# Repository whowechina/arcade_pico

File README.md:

# Arcade Pico - An Alternative Switch/Lamp Holder for Arcade Buttons
[点这里可以切换到中文版](README_CN.md)

It's the successor to my sanwa_opt project. With it, you can use regular low-profile keyboard switches (or even optical sensors) on arcade buttons.

## Features
* Compatible with both old Sanwa (push-click) and new Sanwa (twist-lock), Samducksa, and common Chinese buttons;
* Supports mechanical switches, optical sensors, and magnetic switches (`IO Board` required);
* Mechanical switch can be hotswap (Kailh Choc sockets);
* Feel switch and actuation switch can be separated;
* RGB LED support (`IO Board` required);
* FDM 3D-printing friendly.
* Multiple connection options to fit different systems.

## Thanks
Thanks to many respectful guys/companies who made their tools or materials free or open source (KiCad, OnShape, InkScape, Raspberry things).

Special thanks to community projects and developers.
And also these projects:
* RP_Silicon_KiCad: https://github.com/HeadBoffin/RP_Silicon_KiCad

## My Other Projects
You can check out my other cool projects.

* Popn Pico: https://github.com/whowechina/popn_pico
* IIDX Pico: https://github.com/whowechina/iidx_pico
* IIDX Teeny: https://github.com/whowechina/iidx_teeny
* Chu Pico: https://github.com/whowechina/chu_pico
* Mai Pico: https://github.com/whowechina/mai_pico
* Diva Pico: https://github.com/whowechina/diva_pico
* AIC Pico: https://github.com/whowechina/aic_pico
* Groove Pico: https://github.com/whowechina/groove_pico
* Geki Pico: https://github.com/whowechina/geki_pico
* Musec Pico: https://github.com/whowechina/musec_pico
* Ju Pico: https://github.com/whowechina/ju_pico
* Bishi Pico: https://github.com/whowechina/bishi_pico
* Nos Pico: https://github.com/whowechina/nos_pico
* Voltex Pico: https://github.com/whowechina/voltex_pico
* Chord Pico: https://github.com/whowechina/chord_pico
* Arcade Pico: https://github.com/whowechina/arcade_pico

## **Disclaimer** ##
I made this project in my personal time with no financial benefit or sponsorship. I will continue to improve the project. I have done my best to ensure that everything is accurate and functional, there's always a chance that mistakes may occur. I cannot be held responsible for any loss of your time or money that may result from using this open source project. Thank you for your understanding.

## About the License
It's CC-NC. So DIY for yourself and for your friend, don't make money from it. And plagiarism that doesn’t even dare to mention the original author is not acceptable. Please note that pooling orders and group buying for raw materials is acceptable.Selling any leftover components at cost (without profit) is also acceptable.

If you're interested in buying from me, or for commercial use, please contact me (Discord, QQ group, Goofish).
* My Discord Invitation: https://discord.gg/M8f2PPQFEA
* QQ Group: 854535476
* Goofish: whowe12345

## Use Cases
### Terminology First
* **`Main Board`** - The original controller board or IO board of your arcade system.
* **`Button Board`** - The PCB that contains the switch and LED daughter board. It's the major part of the Arcade Pico project.
* **`IO Board`** - The optional PCB that converts Hall effect switch signals to digital signals, and bridges regular LED signals to WS2812B RGB LED data signals. It's also part of the Arcade Pico project. It cannot replace your original `Main Board`.
* **`Lamp Holder`** - More accurately, it's a base equipped with both lamp and switch, but commonly referred to as lamp holder.

### Case: Replace the Lamp/Switch Holder without the `IO Board`
It's the most common and easy case. The only thing you need to do is wiring the switch and LED signals from your `Main Board` to the corresponding connectors on the `Button Board`.
You can use mechanical switches or optical sensors, but you can't use magnetic switches or RGB lights.

#### Wiring:
* **SW Out** (SH1.0 3P) on `Button Board` → **Button Input** on `Main Board`
* **LED In** (SH1.0 3P) on `Button Board` ← **Lamp Output** on `Main Board`

### Case: Enjoy the Magnetic Switch or the RGB light with the `IO Board`
With magnetic switch, you can define your trigger and reset distance. With RGB light, you can define your button light color and effect. `IO Board` is required to drive the magnetic switch and RGB light.

#### Wiring:
* Magnetic switch signals
  * **SW Out** (SH1.0 3P) on `Button Board` → **Hall In** (SH1.0 3P) on `IO Board`
  * **Out** (XH2.5 2P) on `IO Board` → **Button Input** on `Main Board`
* RGB LED signals
  * **Lamp Output** on `Main Board` → **Lamp In** (XH2.5 2P) on `IO Board`
  * **LED Out** (SH1.0 3P) on `IO Board` → **LED In** (SH1.0 3P) on `Button Board`
  * **LED Out** (SH1.0 3P) on `Button Board` → **LED In** (SH1.0 3P) on next `Button Board` (if any)
  * **LED Out** (SH1.0 3P) on last `Button Board` → **LED End** (SH1.0 3P) on `IO Board` for power backup.

* You can power the `IO Board` from the `Main Board`'s 5V supply via JST 2P, or directly via Type-C port (USB or power adapter).

#### When `IO Board` is connected to a host computer via Type-C:
  * `IO Board` works as an HID device.  
    So if you're fine with this extra USB cable, you might be able to skip the wiring between the `IO Board` and the `Main Board`. However, some games require the controller to be a single device, so this won't work in those cases.
  * CLI (command line interface) is on USB CDC (serial).
  * The Type-C port is also for firmware update.

### Imagined Case: Interfacing with DJDao PhoenixWAN
This is a theoretical case that probably won't be implemented. If implemented, all that cockamamie wiring between `IO Board` and `Main Board` would be eliminated - they'd simply communicate via UART.

Let's hope this happens someday.

# How to Build
## The Button Board
### Common Part
* The PCB gerber file is `Production/PCB/"arcade_pico_button_*.zip`. The one with `socket` is hotswap (for Choc V1 and V2). I always use JLC (https://www.jlcpcb.com) and Jiepei (https://www.jiepei.com), feel free to use your preferred PCB manufacturer. They may ask if you need half-hole pads for the `Button Board`, just answer "No", it's costy and not necessary.
* 2X 3P SH1.0 horizontal SMD connector on "SW" and "LED In" footprints.
* 1X 3P SH1.0 horizontal SMD connector on "LED Out" footprint, only needed when using WS2812B RGB LED daughter board.

* To connect LEDs:
  * "LED In" connector (+, -) is for regular single color LED signal from your existing `Main Board`.
  * "LED In" and "LED Out" connectors are for daisy-chain when using WS2812B RGB LED daughter board.

### Mechanical Switch
* Use either SW1 or SW2 footprint for Kailh Choc V1/V2 switches.
* Use Kailh Choc low-profile hotswap socket if you choose hotswap PCB version.  
  https://kailhswitch.net/products/kailh-mechnical-keyboard-switches-hot-swap-pcb-socket-diy-for-1350-choc-low-profile-keyboard-switches
* Short the corresponding jumper (sw1 or sw2) to enable the switch.
* You can solder the other switch, but it's only for the feel, so don't short the jumper.

* To connect to controller's `Main Board`:
  * "SW" connector (Out, GND) is for the switch signal;

* This example shows SW1 as the trigger switch, and optional Choc V1 on SW2 is just for the feel.  

### Optical Sensor (IR Diode + Phototransistor)
* Solder the IR diode (IR908-7C) and phototransistor (PT908-7C) at proper height;
* Solder R3 (500 ohm for 3.3V supply, 1k ohm for 5V supply);
* Resistors: R4, R5; Jumpers: c, e; Zener: Z1.
  * Low-active logic (most systems are): R4 (0-10 ohm), R5 (2k ohm), short the jumper e by soldering.
  * High-active logic: R4 (2k ohm), R5 (0-10 ohm), short the jumper c.
  * When power supply is 5V but the target system IO is 3.3V, solder Z1 (3.3V SOD-123F Zener diode) to protect the IO pin.
* You can solder a mechanical switch on SW1 footprint for some tactile feel, but don't short the jumper sw1.
* On most systems, LED positive line is a constant 5V or 3.3V power supply, you can borrow that to power the optical sensor - just short the jumper "LEDP-V".

* To connect to controller's `Main Board`:
  * "SW" connector (V, Out, GND) is for the switch signal;

* This example shows a low-active configuration, 5V is borrowed from LED positive line, and optional Choc V1 on SW1 just for the feel.  

### Magnetic (Hall Effect) Switch
* Magnetic switch is on SW1 footprint.
* Solder U1 (SS49E SOT23-3) and C1 (0.1uF 0603).
* You can install a mechanical switch on SW2 footprint for some tactile feel, but don't solder the jumper.
* If the Hall effect switch is not mounted tightly, you may need to use some RTV silicone adhesive to secure it.

* This example uses Hall effect switch on SW2 and optional Choc V1 on SW1 just for the feel.  

* To connect to controller's `Main Board`:
* "SW" connector (V, Out, G) connects to the **Arcade Pico IO** board. Then the `IO Board` connects to the `Main Board`.

* Note that Arcade Pico `IO Board` is need for this setup.

## The LED Daughter Board
* It is separated from the **Arcade Pico Button** board by snapping or cutting. There're two versions: single-color LED and WS2812B RGB LED. You can choose either one according to your needs.
* After soldering the components, insert the LED daughter board back to the button PCB vertically from the top side. Solder one pin first, so you'll have a chance to adjust the height.
* If it's too low or too high, you won't get even illumination. You can measure the height from your old lamp holder. From my experience with Sanwa, distance from the LED top to the PCB surface is about 37mm.
* When you finish adjusting the height, solder all pins to secure the connection.  

### Single-color LED Board
* Use high-brightness side emitting LEDs. The footprint is compatible with various packages, such as SMD 4008, SMD 4020, SMD 3014, or even through-hole ones (ones with concave lens are better).
* If you're using SMD LEDs, you can use two of them, one for each side, to get better light distribution.
* They're normally rated for 20mA current. So typically you use 100-220 ohm current resistors (R1 and R2) for 5V supply, or 50-100 ohm for 3.3V supply.
* Here's how it looks after soldered.  
    
* If the polarity of the LED footprint doesn't match your LED, just cut/break the copper trace right at the "x" mark at **both sides**, and short the jumpers accordingly. This will reverse the polarity.  

### WS2812B RGB LED Board
* **Arcade Pico `IO Board` is required.**
* Use WS2812B 4020 side emitting RGB LEDs. You can use two of them, one for each side, to get better light distribution.
* 0.1uF 0805 or 0603 capacitor on C2 footprint is highly recommended.
* Here's how it looks after soldered.  

## The `IO Board`
* The `IO Board` can convert the analog signals from Hall effect switches into digital signals for your main controller board. It can also bridge traditional LED bulb signals to WS2812B RGB LED data signals.
* If you don't need one or both of these functions, just skip the corresponding components.

### Common Parts
* 1x Raspberry Pi Pico.  
  https://www.raspberrypi.com/products/raspberry-pi-pico
* 2x 2P JST XH2.54 or XH2.5 vertical connectors, for 5V power input.
* 1x 3P JST XH2.54 or XH2.5 vertical connector for UART, optional for future use.

### Components for Hall Effect Switch
* 1x ADG708BRUZ, 8 to 1 analog switch, in TSSOP-16 (U3).
* 1x LP5907MFX-4.5 or TPS7A2042PDBVR LDO, in SOT23-5 (U2), see next line.
* 1x LM4040 shunt voltage reference in SOT23-3 (Z2), 2.0~2.1V (for 4.2V LDO) or 2.2~2.5V (for 4.5V LDO).
* 1x 3.3V Zener diode, in SOD-123 or SOD-123F, such as BZT52H-C3V3 (Z1).
* 3x 0.1uF 0603 capacitors (CC1, CC2, CC3).
* 8x 3P SH1.0 horizontal SMD connectors (In1~In8), for connecting up to 8 Hall effect `Button Board`s.
* 8x 2P JST XH2.54 or XH2.5 vertical connectors (Out1~Out8), for connecting to the main controller board.

### Components for RGB LED
* 8x 220ohm 0603 resistors (R1~R8), for optical isolator current limiting. If your light is 12V, use 1kohm 0805 resistors instead.
* 8x 1N4148 SOD-323 diodes (D1~D8), to protect from reverse voltage, only needed for 12V light input.
* 2X PC847 or compatible quad optical isolators (U4, U5), in SOP-16.
* 2x 0805 x 4 5.1K 8P4R resistor arrays (RN1, RN2), if they're not available, use 8x individual 5.1K 0603 resistors instead.
* 2x 3P SH1.0 horizontal SMD connectors (LED Out and LED End), to connect to the `Button Board` equipped with WS2812B RGB LED daughter board.
* 8x 2P JST XH2.54 or XH2.5 vertical connectors (Lamp In 1~8), for connecting to the main controller board's LED signal.

## Notes on PCB and Electronics
### Things You May **Need** to Tinker with
* Here's how you calculate the LED current limiter, it also applies to the IR emitter diode of the optical isolator:
  * R = (V_supply - V_F) / I
  * V_F for single color LED is usually around 3V, V_F for IR emitter is usually around 1.3V.
  * I for single color LED is usually 10-20mA, I for IR emitter is practically 1-10mA.
* Here's how you calculate the pull-up or pull-down resistor for phototransistor (the one on the `Button Board` and the one inside the optical isolator):
  * R >= V_supply / I_C
  * It's difficult to estimate the I_C (collector current) of the phototransistor, so just assume it's around 1mA.
  * So on a 3.3V power supply, R >= 3.3V / 1mA = 3.3K ohm, You can use a 3.3K or 3.9K ohm resistor.
  * You may need to adjust the resistor value according to your actual setup.

### Things You May **Want** to Tinker with
* For the "feel switch", choose clicky ones, Choc V1 and Choc V2 both have some clikcy options. If you find other low-profile mechanical switches which fit in the footprint, you can try them too.
* When Hall effect switch and the "feel" switch is both installed, spring force adds up, you may want to use a lighter spring for both of them. You can choose light force switches, or you can change the spring inside them.

## The Holder Body
* Use any FDM printer to print the body.
  * Material: PLA, PETG, ABS, you name it.
  * Layer Height: 0.2mm is recommended.
  * Infill: 20% is enough.
  * Walls: 2-4 perimeters.
  * Support: Yes, tree support.

* Files are in the "Production/3DPrint" folder.
  * `Sanwa_push.stl` - old style Sanwa lamp holder (push-click type).
  * `Sanwa_twist.stl` - new style Sanwa lamp holder (twist-lock type).
  * `Samducksa.stl` - Samducksa lamp holder.
  * `Chinese.stl` - common Chinese button lamp holder.

* Use M2\*6mm screws to secure the PCB to the button.

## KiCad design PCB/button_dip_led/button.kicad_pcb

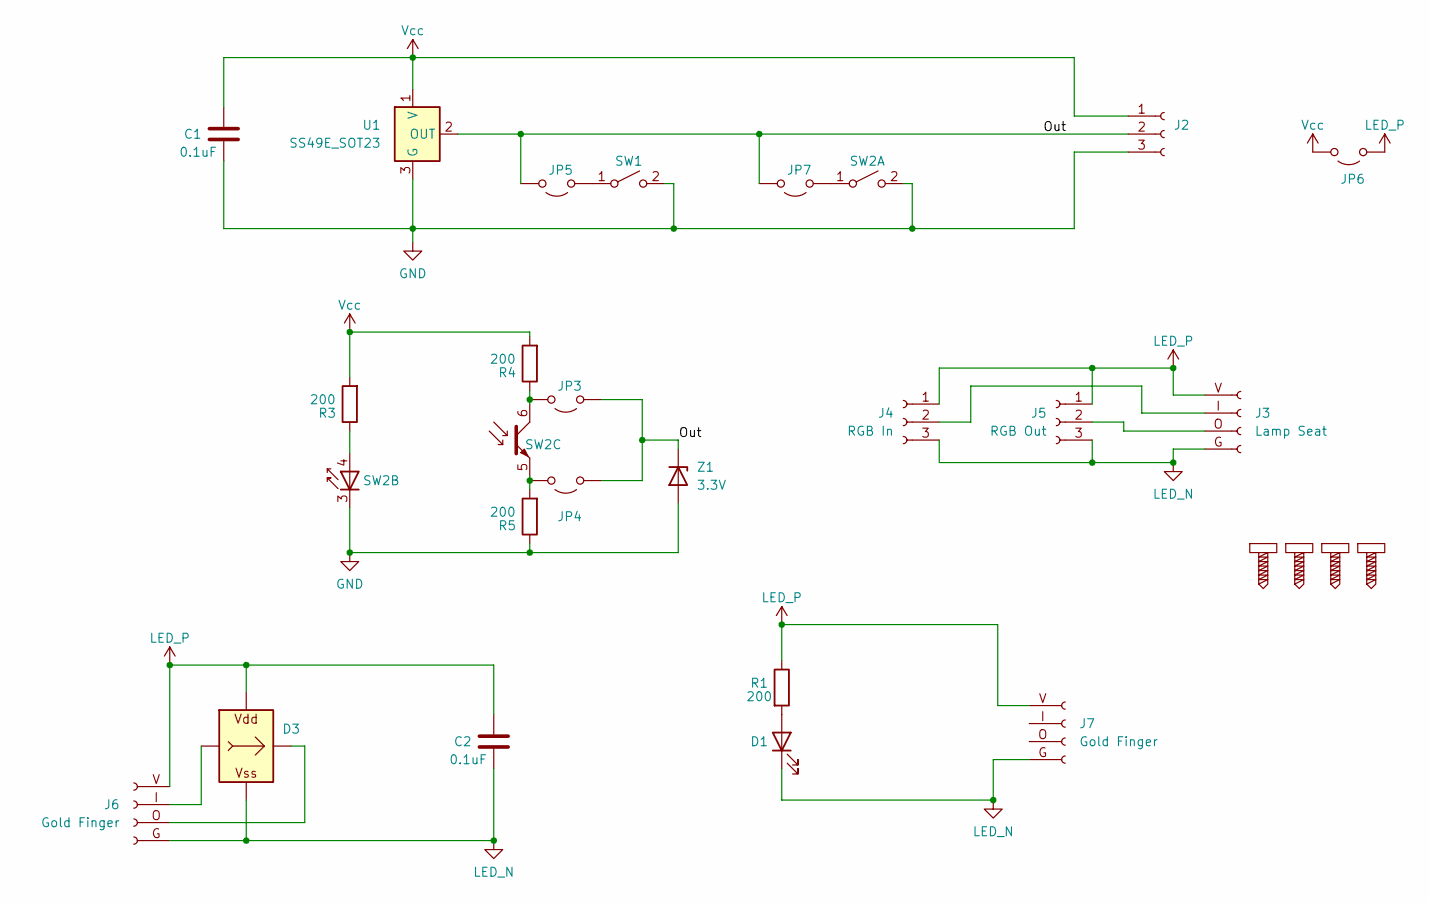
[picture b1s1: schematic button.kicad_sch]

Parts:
C1: 0.1uF; C_0603_1608Metric_Pad1.08x0.95mm_HandSolder
C2: 0.1uF; C_0805_2012Metric_Pad1.18x1.45mm_HandSolder
D1: LED; DIPLED
D3: WS2812B_Unified; WS2812B-DIP
J2: Conn_01x03_Socket; SH1.0_3P_Solder_Combo
J3: Lamp Seat; LampSeat
J4: RGB In; SH1.0_3P_Solder_Combo
J5: RGB Out; SH1.0_3P_Solder_Combo
J6, J7: Gold Finger; GoldFinger
JP3: c; SolderJump
JP4: e; SolderJump
JP5: sw1; SolderJump
JP6: LEDP-V; SolderJump
JP7: sw2; SolderJump
R1, R3: 200; R_0805_2012Metric_Pad1.20x1.40mm_HandSolder
R4, R5: 200; R_0805_2012Metric
S1, S2, S3, S4: M2_Screw
SW1: Choc_HE
SW2: Choc and IR Pair; SW_Kailh_Choc_IR_Combo
U1: SS49E_SOT23; SOT-23-FAT
Z1: 3.3V; D_SOD-123F

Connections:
/Out: J2.2, JP3.1 (A), JP4.1 (A), JP5.2 (B), JP7.2 (B), U1.2 (OUT), Z1.1 (K)
GND: C1.1, J2.3, R5.1, SW1.2 (B), SW2.2 (B), SW2.3 (K), U1.3 (G), Z1.2 (A)
LED_N: C2.1, D1.1 (K), D3.G (VSS), J3.G, J4.3, J5.3, J6.G, J7.G
LED_P: C2.2, D3.V (VDD), J3.V, J4.1, J5.1, J6.V, J7.V, JP6.1 (A), R1.1
unnamed: D1.2 (A), R1.2
unnamed: D3.I (In), J6.I (In)
unnamed: D3.O (Out), J6.O (Out)
unnamed: J3.I (In), J4.2
unnamed: J3.O (Out), J5.2
unnamed: JP3.2 (B), R4.1, SW2.6 (C)
unnamed: JP4.2 (B), R5.2, SW2.5 (E)
unnamed: JP5.1 (A), SW1.1 (A)
unnamed: JP7.1 (A), SW2.1 (A)
unnamed: R3.1, SW2.4 (A)
Vcc: C1.2, J2.1, JP6.2 (B), R3.2, R4.2, U1.1 (V)

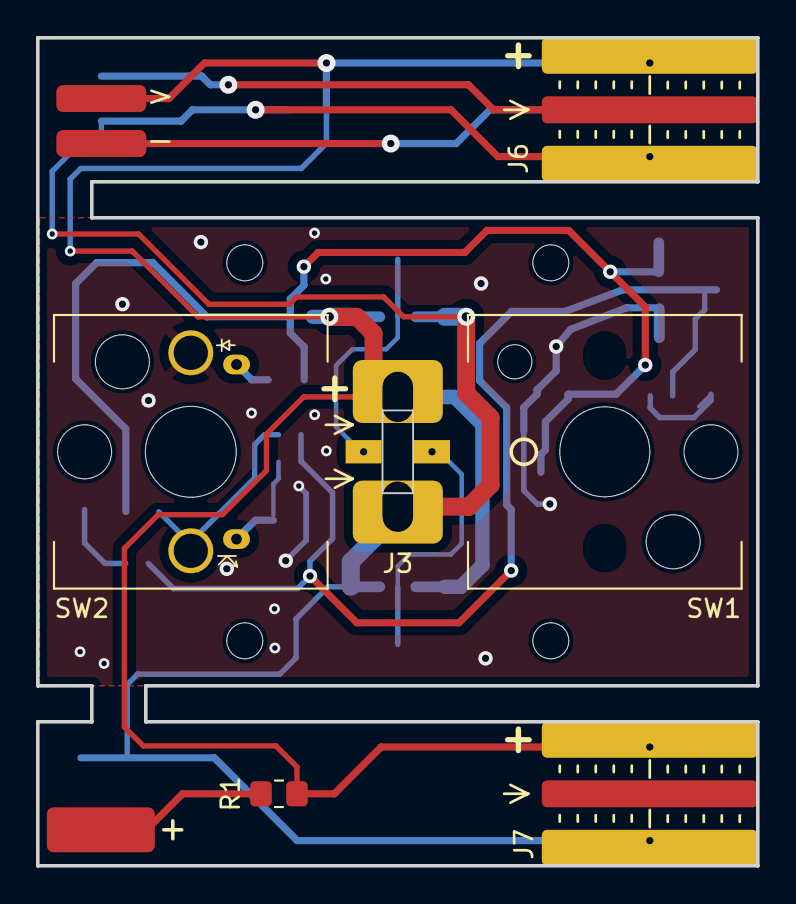
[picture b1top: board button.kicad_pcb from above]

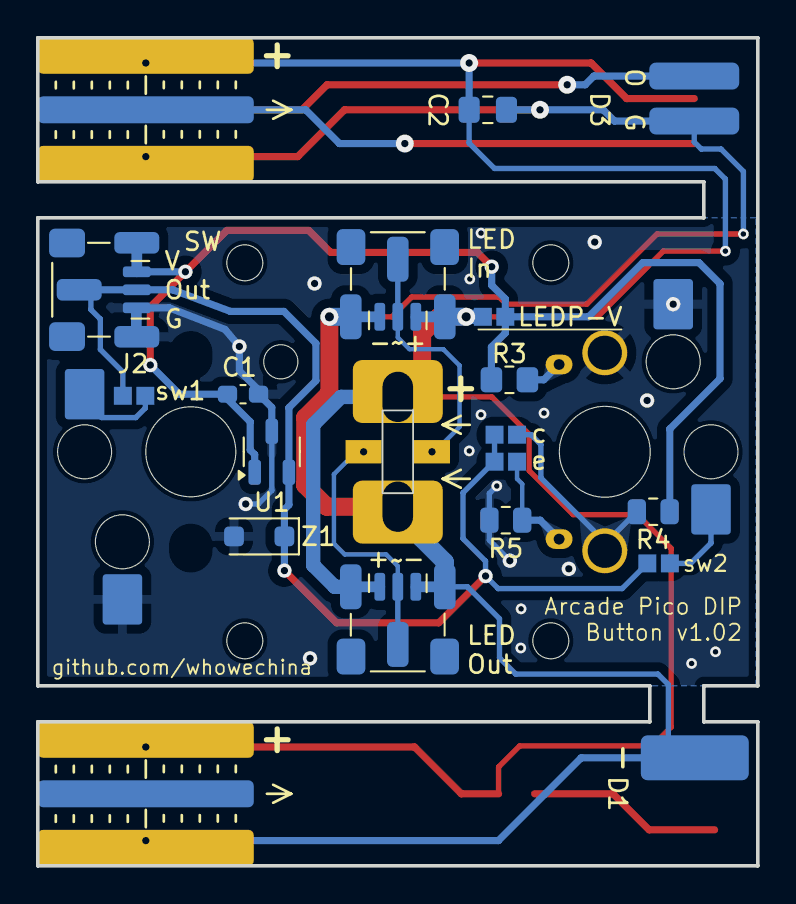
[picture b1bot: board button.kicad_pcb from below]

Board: 2 copper layers, 40.0 x 46.0 mm, 27 parts (17 on the bottom side), 15 nets.

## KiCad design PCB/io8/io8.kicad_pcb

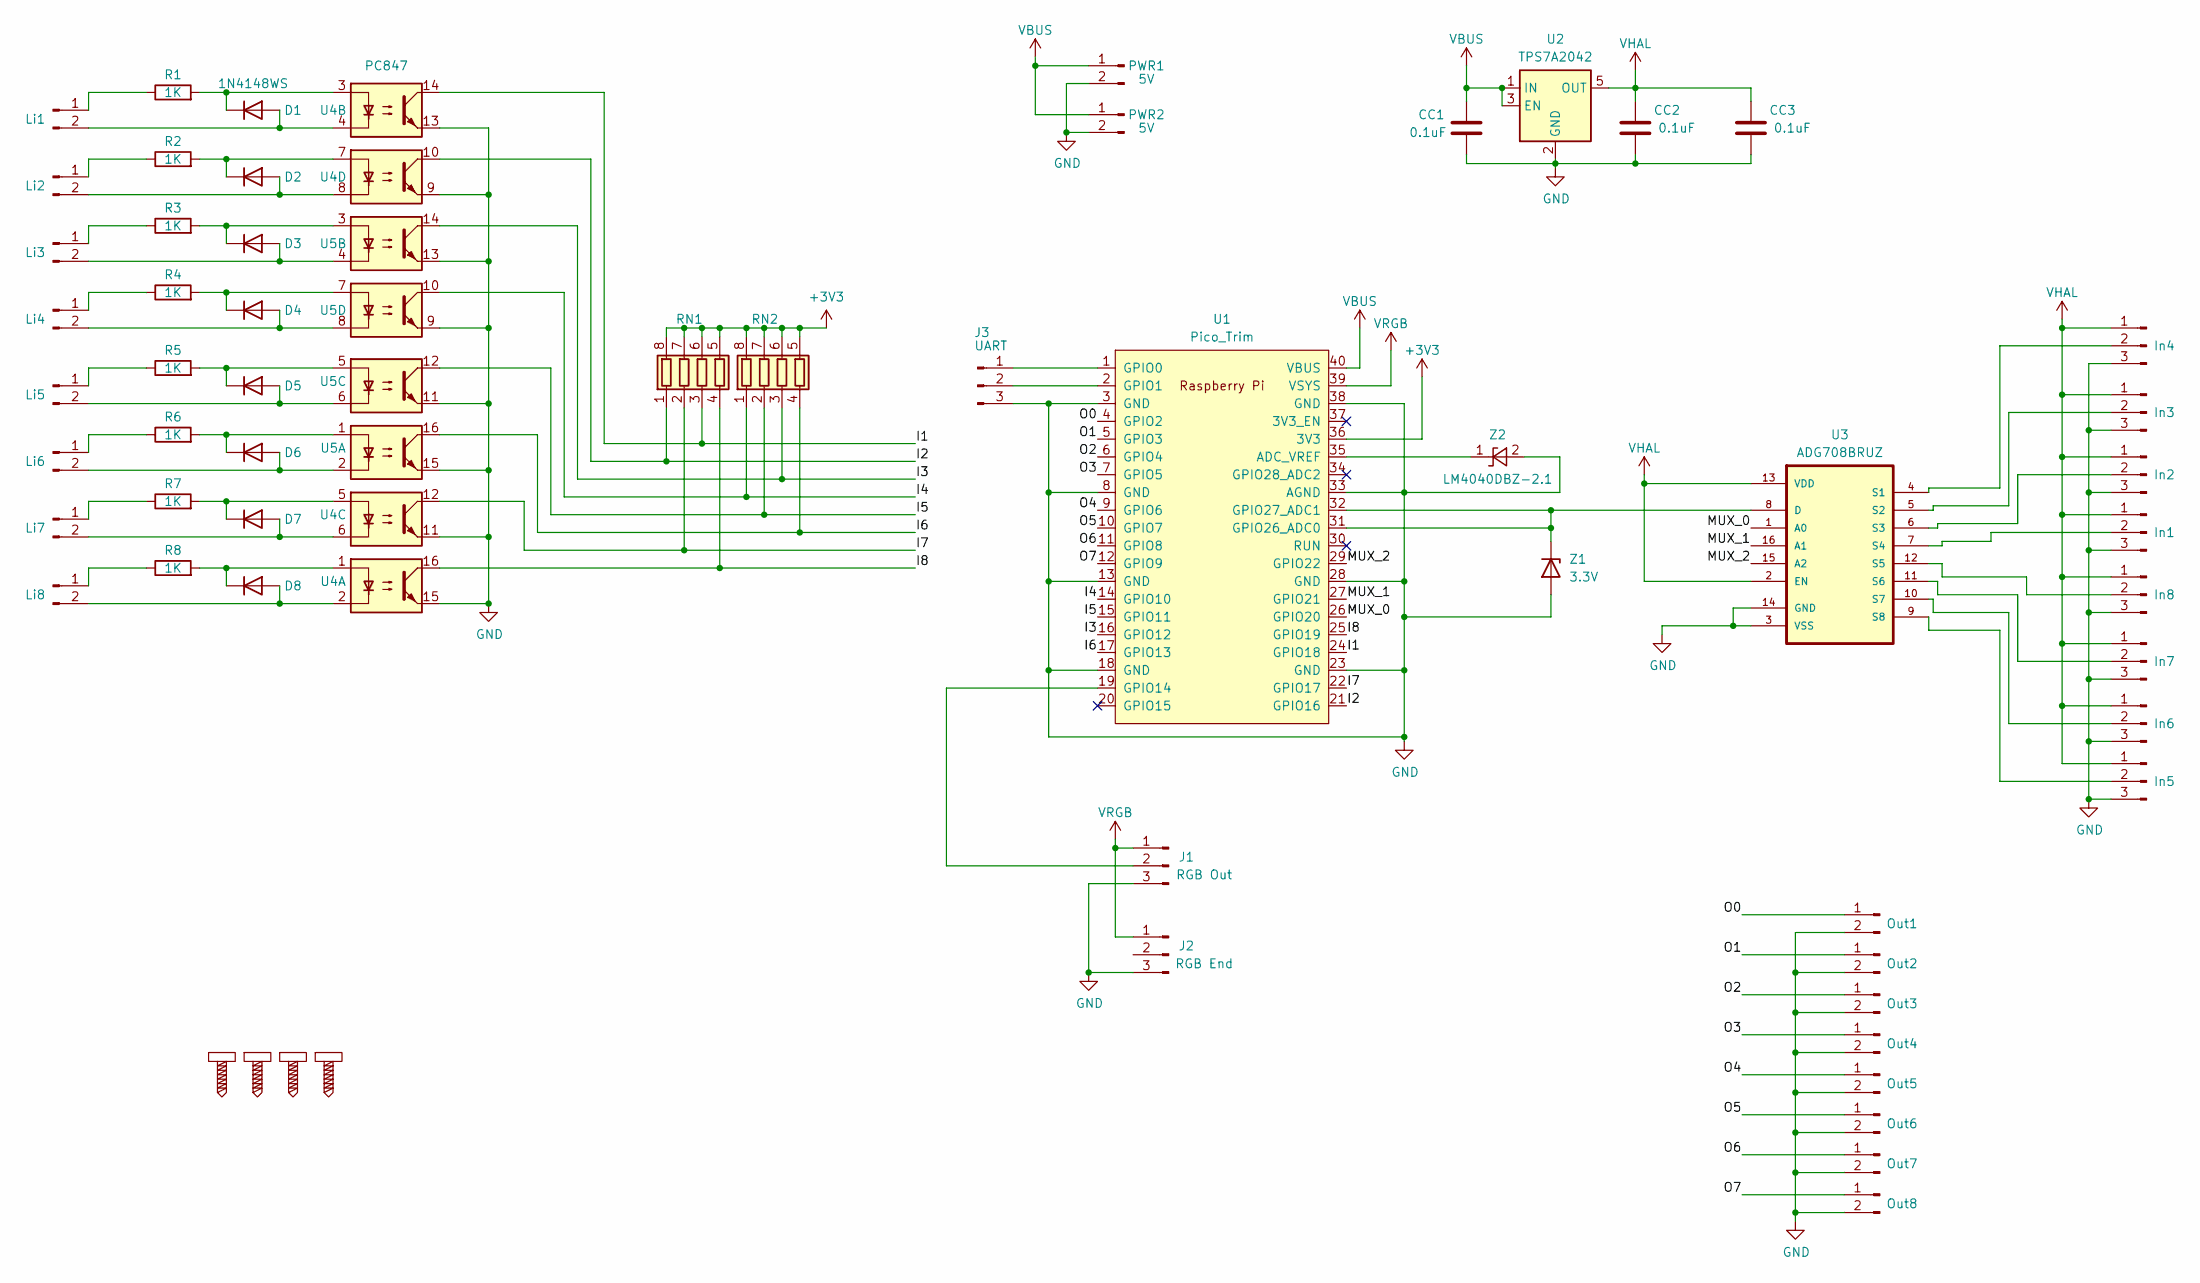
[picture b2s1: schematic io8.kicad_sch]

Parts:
CC1, CC2, CC3: 0.1uF; C_0603_1608Metric_Pad1.08x0.95mm_HandSolder
D1, D2, D3, D4, D5, D6, D7, D8: 1N4148WS; D_SOD-323_FAT
In1, In2, In3, In4, In5, In6, In7, In8: Conn_01x03_Pin; SH1.0_3P_Solder_Combo
J1: RGB Out; SH1.0_3P_Solder_Combo
J2: RGB End; SH1.0_3P_Solder_Combo
J3: UART; JST_XH_B3B-XH-A_1x03_P2.50mm_Vertical
Li1, Li2, Li3, Li4, Li5, Li6, Li7, Li8: Conn_01x02_Pin; JST_XH_B2B-XH-A_1x02_P2.50mm_Vertical
Out1, Out2, Out3, Out4, Out5, Out6, Out7, Out8: Conn_01x02_Pin; JST_XH_B2B-XH-A_1x02_P2.50mm_Vertical
PWR1, PWR2: 5V; JST_XH_B2B-XH-A_1x02_P2.50mm_Vertical
R1, R2, R3, R4, R5, R6, R7, R8: 1K; R_0805_2012Metric_Pad1.20x1.40mm_HandSolder
RN1, RN2: R_Pack04; R_Array_Convex_4x0805
S1, S2, S3, S4: M3_Screw
U1: Pico_Trim; RPi_Pico_SMD_No_USB
U2: TPS7A2042; SOT-23-5
U3: ADG708BRUZ; TSSOP-16_4.4x5mm_P0.65mm
U4, U5: PC847; SOP-16_4.4x10.4mm_P1.27mm
Z1: 3.3V; D_SOD-123F
Z2: LM4040DBZ-2.1; SOT-23-FAT

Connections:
+3V3: RN1.5 (R4.2), RN1.6 (R3.2), RN1.7 (R2.2), RN1.8 (R1.2), RN2.5 (R4.2), RN2.6 (R3.2), RN2.7 (R2.2), RN2.8 (R1.2), U1.36 (3V3)
/I1: RN1.3 (R3.1), U1.24 (GPIO18), U4.14
/I2: RN1.1 (R1.1), U1.21 (GPIO16), U4.10
/I3: RN2.3 (R3.1), U1.16 (GPIO12), U5.14
/I4: RN2.1 (R1.1), U1.14 (GPIO10), U5.10
/I5: RN2.2 (R2.1), U1.15 (GPIO11), U5.12
/I6: RN2.4 (R4.1), U1.17 (GPIO13), U5.16
/I7: RN1.2 (R2.1), U1.22 (GPIO17), U4.12
/I8: RN1.4 (R4.1), U1.25 (GPIO19), U4.16
/MUX_0: U1.26 (GPIO20), U3.1 (A0)
/MUX_1: U1.27 (GPIO21), U3.16 (A1)
/MUX_2: U1.29 (GPIO22), U3.15 (A2)
/O0: Out1.1, U1.4 (GPIO2)
/O1: Out2.1, U1.5 (GPIO3)
/O2: Out3.1, U1.6 (GPIO4)
/O3: Out4.1, U1.7 (GPIO5)
/O4: Out5.1, U1.9 (GPIO6)
/O5: Out6.1, U1.10 (GPIO7)
/O6: Out7.1, U1.11 (GPIO8)
/O7: Out8.1, U1.12 (GPIO9)
GND: CC1.2, CC2.2, CC3.2, In1.3, In2.3, In3.3, In4.3, In5.3, In6.3, In7.3, In8.3, J1.3, J2.3, J3.3, Out1.2, Out2.2, Out3.2, Out4.2, Out5.2, Out6.2, Out7.2, Out8.2, PWR1.2, PWR2.2, U1.3 (GND), U1.8 (GND), U1.13 (GND), U1.18 (GND), U1.23 (GND), U1.28 (GND), U1.33 (AGND), U1.38 (GND), U2.2 (GND), U3.3 (VSS), U3.14 (GND), U4.9, U4.11, U4.13, U4.15, U5.9, U5.11, U5.13, U5.15, Z1.2 (A), Z2.2 (A)
unnamed: D1.2 (A), Li1.2, U4.4
unnamed: D1.1 (K), R1.2, U4.3
unnamed: D2.2 (A), Li2.2, U4.8
unnamed: D2.1 (K), R2.2, U4.7
unnamed: D3.2 (A), Li3.2, U5.4
unnamed: D3.1 (K), R3.2, U5.3
unnamed: D4.2 (A), Li4.2, U5.8
unnamed: D4.1 (K), R4.2, U5.7
unnamed: D5.2 (A), Li5.2, U5.6
unnamed: D5.1 (K), R5.2, U5.5
unnamed: D6.2 (A), Li6.2, U5.2
unnamed: D6.1 (K), R6.2, U5.1
unnamed: D7.2 (A), Li7.2, U4.6
unnamed: D7.1 (K), R7.2, U4.5
unnamed: D8.2 (A), Li8.2, U4.2
unnamed: D8.1 (K), R8.2, U4.1
unnamed: In1.2, U3.7 (S4)
unnamed: In2.2, U3.6 (S3)
unnamed: In3.2, U3.5 (S2)
unnamed: In4.2, U3.4 (S1)
unnamed: In5.2, U3.9 (S8)
unnamed: In6.2, U3.10 (S7)
unnamed: In7.2, U3.11 (S6)
unnamed: In8.2, U3.12 (S5)
unnamed: J1.2, U1.19 (GPIO14)
unnamed: J3.1, U1.1 (GPIO0)
unnamed: J3.2, U1.2 (GPIO1)
unnamed: Li1.1, R1.1
unnamed: Li2.1, R2.1
unnamed: Li3.1, R3.1
unnamed: Li4.1, R4.1
unnamed: Li5.1, R5.1
unnamed: Li6.1, R6.1
unnamed: Li7.1, R7.1
unnamed: Li8.1, R8.1
unnamed: U1.35 (ADC_VREF), Z2.1 (K)
unnamed: U1.31 (GPIO26_ADC0), U1.32 (GPIO27_ADC1), U3.8 (D), Z1.1 (K)
VBUS: CC1.1, PWR1.1, PWR2.1, U1.40 (VBUS), U2.1 (IN), U2.3 (EN)
VHAL: CC2.1, CC3.1, In1.1, In2.1, In3.1, In4.1, In5.1, In6.1, In7.1, In8.1, U2.5 (OUT), U3.2 (EN), U3.13 (VDD)
VRGB: J1.1, J2.1, U1.39 (VSYS)

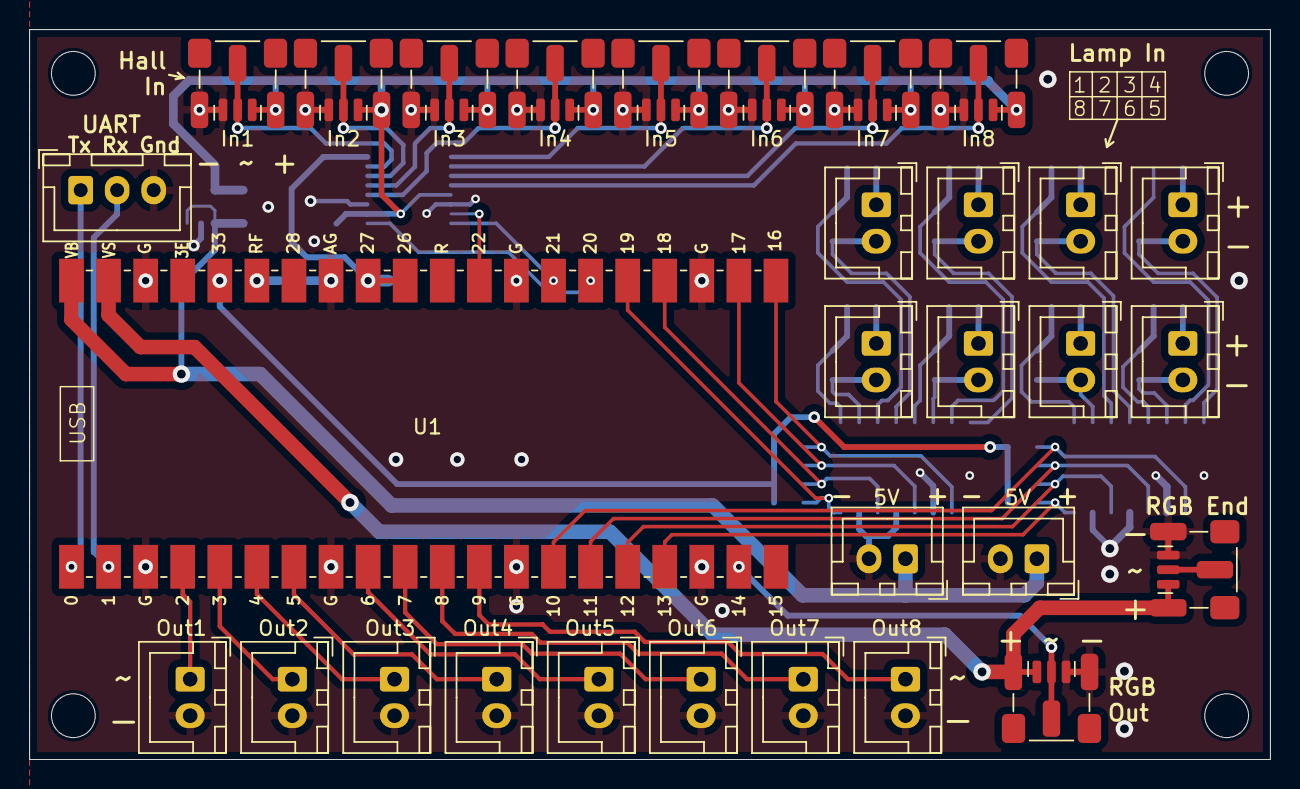
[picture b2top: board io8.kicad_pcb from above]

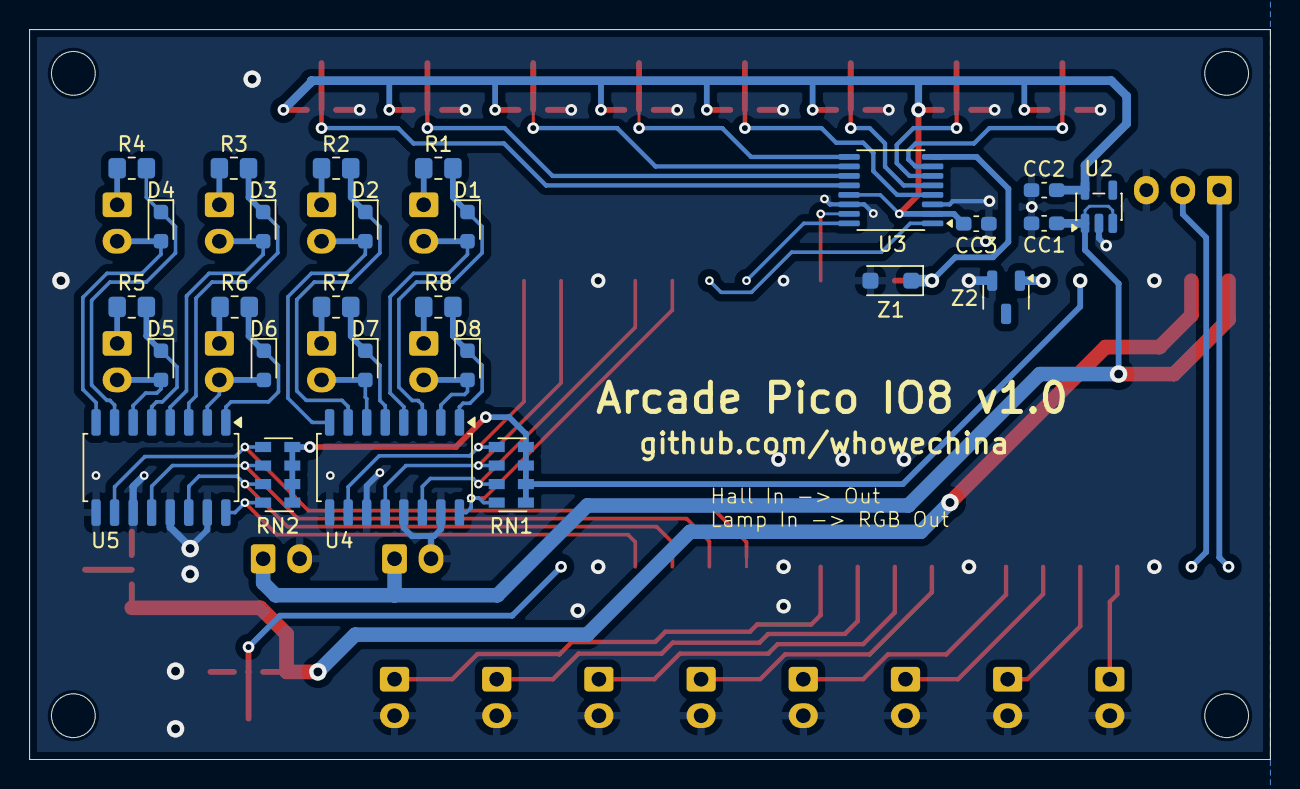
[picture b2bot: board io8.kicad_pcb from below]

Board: 2 copper layers, 85.0 x 50.0 mm, 61 parts (27 on the bottom side), 61 nets.
